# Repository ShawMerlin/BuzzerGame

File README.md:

# BuzzerGame

I modified the below Amazon Buzzers with my own 3 color LED board and Arduino Uno R3 Hat to run them. <br> <br>

The Buttons X LED's will be blue until someone hits one, the one hit will turn Green while the other will turn red <br>
They will stay in this state until the Clear Button is pressed. <br>
This also uses the buzzer from the original game to buzz when they are selected. <br>
Modification of the original button is needed. <br> <br>

https://www.amazon.com/gp/product/B07WJLD44G <br>

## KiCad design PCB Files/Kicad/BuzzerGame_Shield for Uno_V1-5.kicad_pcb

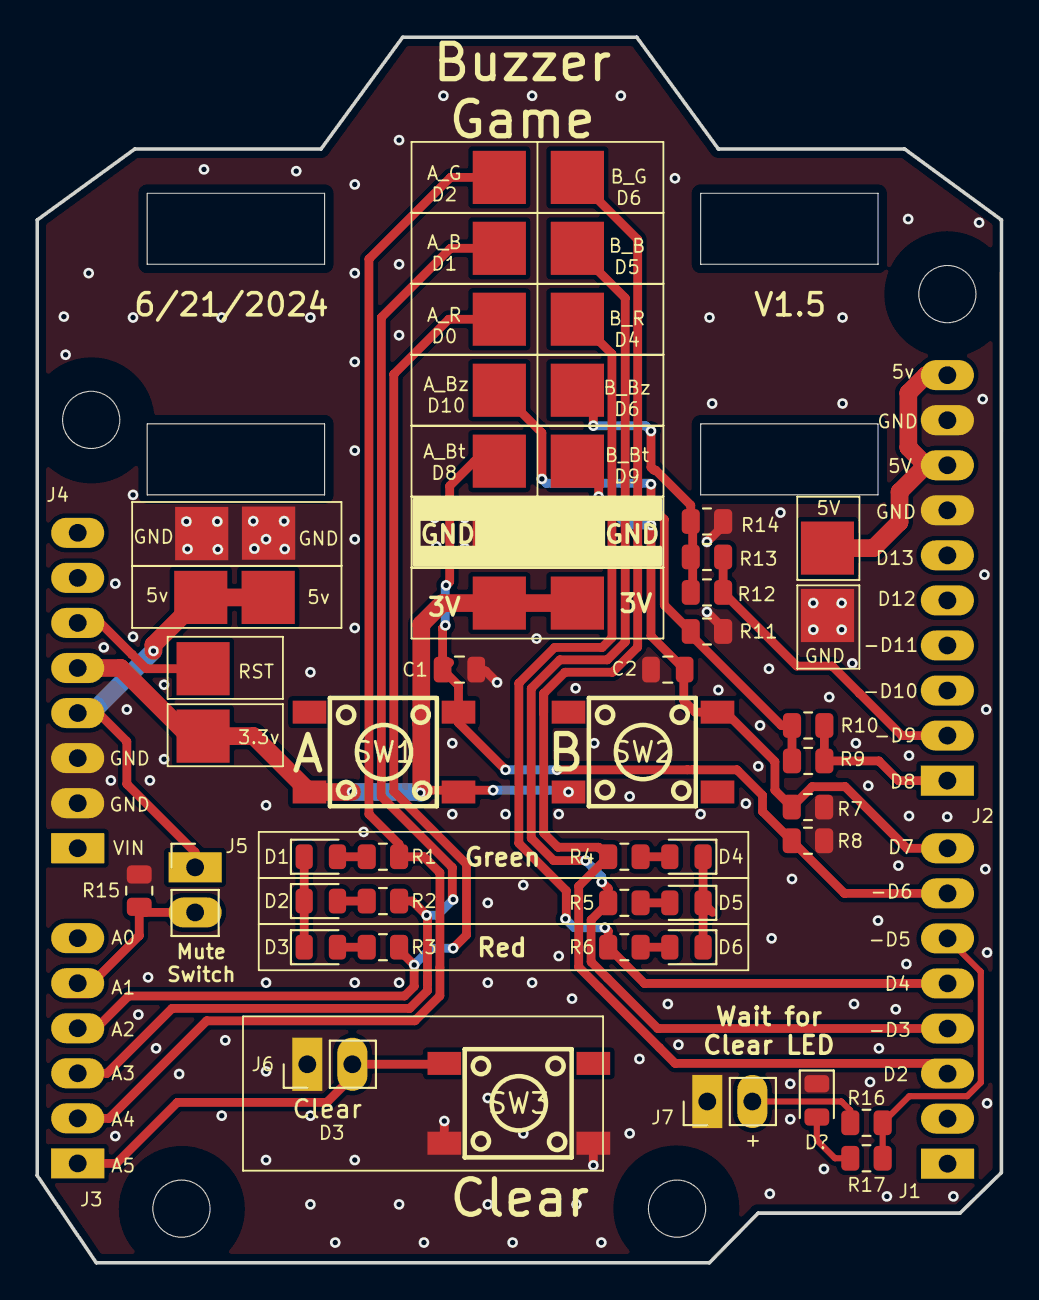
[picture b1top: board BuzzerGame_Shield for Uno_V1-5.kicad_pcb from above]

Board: 2 copper layers, 54.4 x 69.1 mm, 46 parts (0 on the bottom side), 29 nets.

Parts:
C1, C2: 10K; C_0805_2012Metric
D1, D2, D3, D4, D5, D6: Green; LED_0805_2012Metric
D?: White; LED_0805_2012Metric
GND: PinHeader_1x07_P2.54mm_Vertical
GND#2, GND#3: PinHeader_1x07_P2.54mm_Vertical
J1, J1#2, J1#3, J1#5, J1#6, J1#7, J1#8: PinHeader_1x07_P2.54mm_Vertical
J1#4, J4: PinHeader_1x08_P2.54mm_Vertical
J2: PinHeader_1x10_P2.54mm_Vertical
J3: PinHeader_1x06_P2.54mm_Vertical
J5, J6, J7: PinHeader_1x02_P2.54mm_Vertical
R1, R2, R3, R6, R8: 2K; R_0805_2012Metric
R4, R5, R15, R16, R17: 10R; R_0805_2012Metric
R7, R9, R10, R11, R12, R13, R14: 10K; R_0805_2012Metric
SW1, SW2, SW3: KEY-SMD_4P-L6.0-W6.0-P4.50-LS9.0

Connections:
3v: J1#2.3V, J1#3.1, J1#8.1, J4.5, SW1.3, SW1.4, SW2.3
5V: J1#5.5V, J1#6.5V, J1#7.5V, J2.8, J2.10, J4.4, J5.1
ABLUE: J1#8.6, J3.3, R2.2
AGREEN: J1#8.7, J3.2, R1.2
ARED: J1#8.5, J3.4, R3.2
A_Button: C1.2, J1#4.7, J1#8.3, R8.2, SW1.2
A_Buzz_Out: J1#8.4, R9.2, R10.2, R11.2
A_Buzzer: J2.1, R9.1, R10.1
BBLUE: J1#3.6, J1#4.4, R5.2
BGREEN: J1#3.7, J1#4.3, R4.2
BRED: J1#3.5, J1#4.5, R6.2
B_Button1: C2.1, J1#3.3, J1#4.8, R7.2, SW2.2
B_Buzz_Out: J1#3.4, R12.2, R13.2, R14.2
B_Buzzer: J2.2, R12.1, R13.1
Clear1: J3.1, J6.2, SW3.1
GND: C1.1, C2.2, D?.1, GND.GBD, GND#2.GBD, GND#3.GBD, J1#3.2, J1#8.2, J2.7, J2.9, J4.2, J4.3, J6.1, J7.1, R7.1, R8.1, R11.1, R14.1, R15.1, SW3.3, SW3.4
ICC1: D1.2, R1.1
ICC2: D2.2, R2.1
ICC3: D3.2, R3.1
ICC4: D4.2, R4.1
ICC5: D5.2, R5.1
ICC6: D6.2, R6.1
ICC9: D?.2, R17.1
LEDGND: D1.1, D2.1, D3.1
LEDGND1: D4.1, D5.1, D6.1
Mute: J3.5, J5.2, R15.2
RST: J1.RST, J4.6
WFC: J7.2, R16.1
WaitforClear: J1#4.6, R16.2, R17.2
